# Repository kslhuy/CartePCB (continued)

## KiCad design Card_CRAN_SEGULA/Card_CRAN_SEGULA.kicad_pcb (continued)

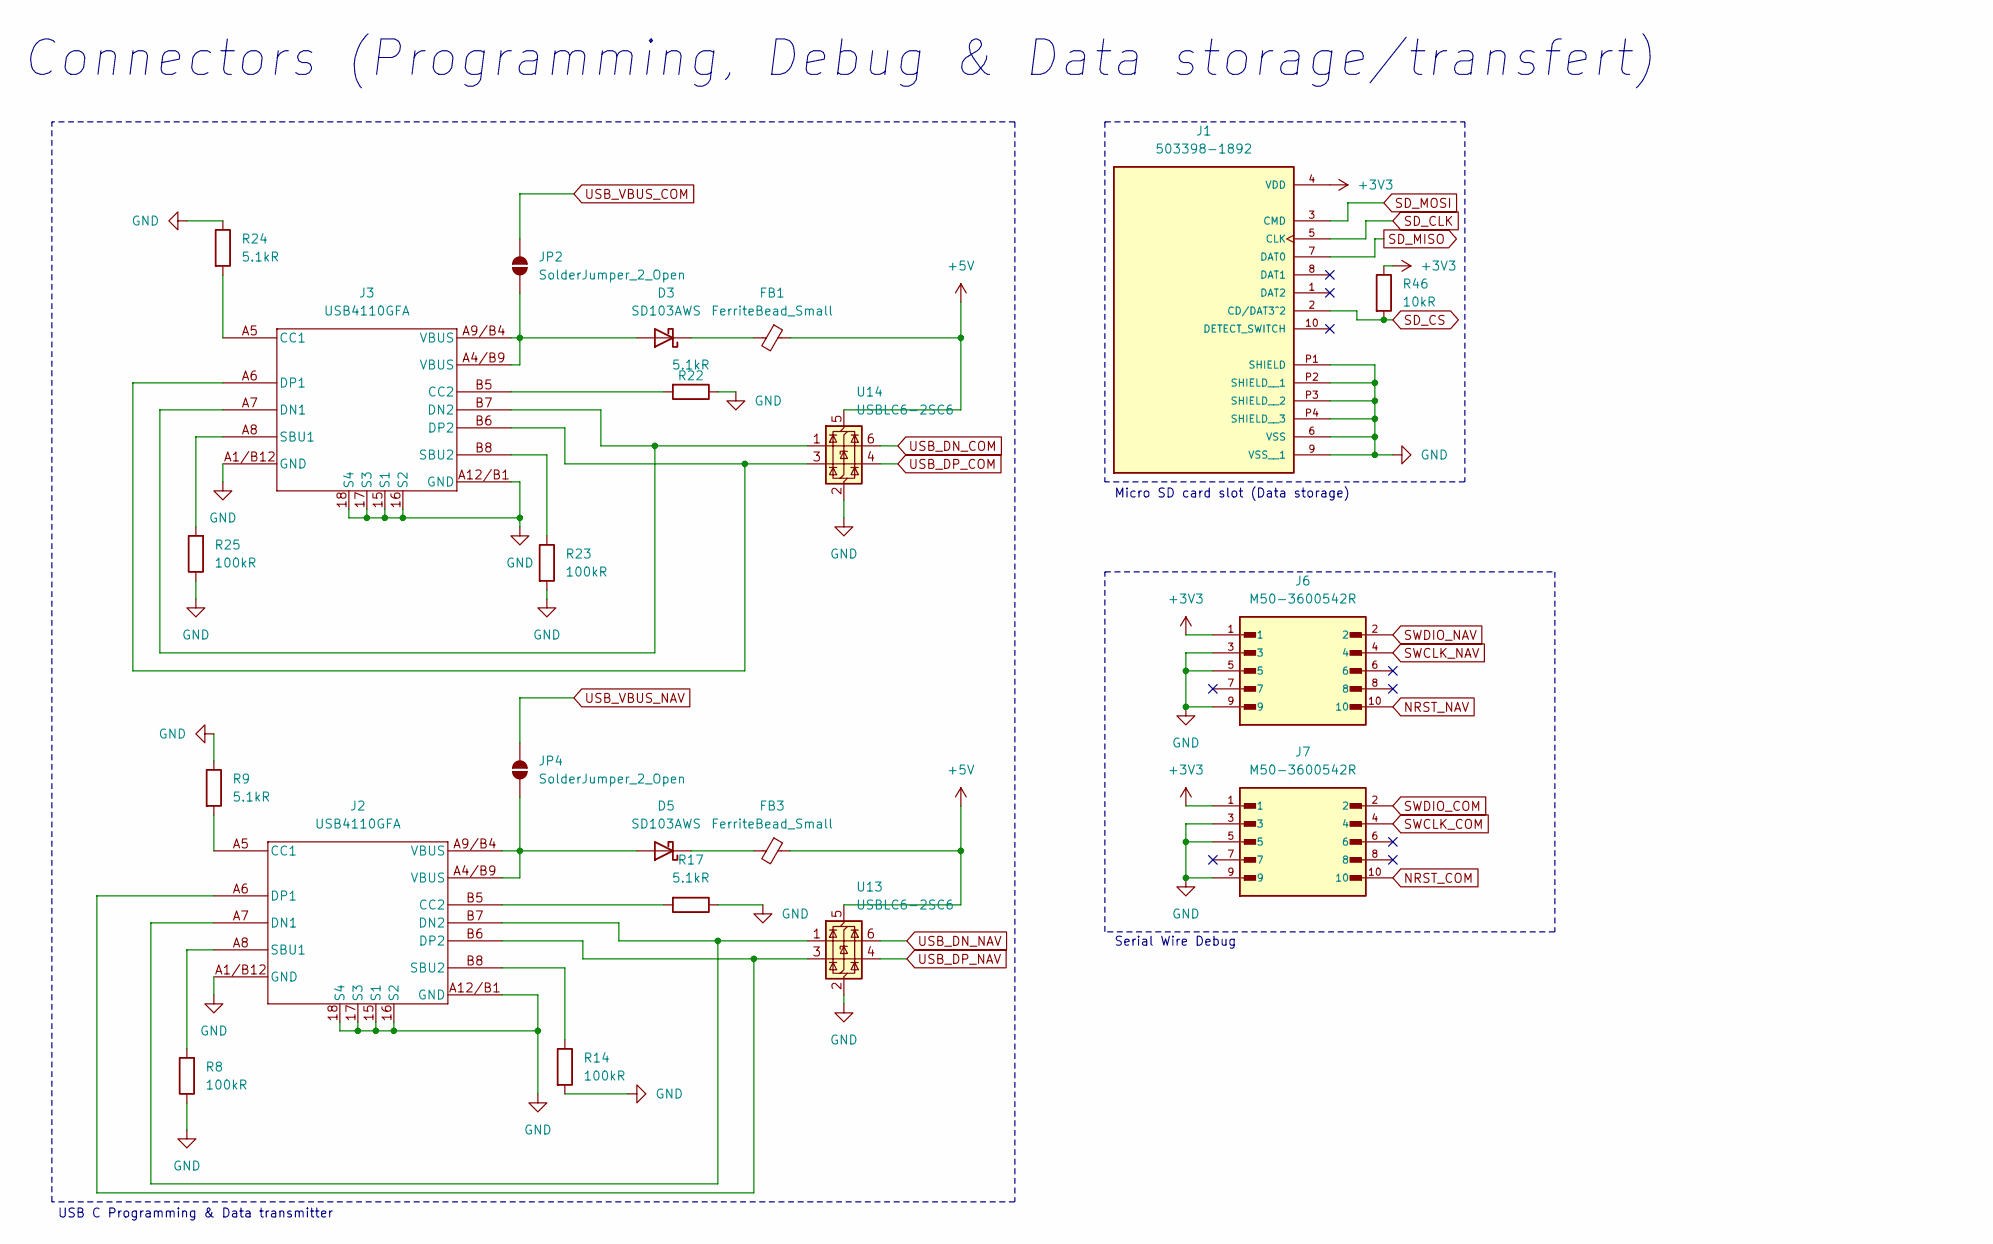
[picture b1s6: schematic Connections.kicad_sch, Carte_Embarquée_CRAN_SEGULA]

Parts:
D3, D5: SD103AWS; D_SOD-323
FB1, FB3: FerriteBead_Small; L_0402_1005Metric
J1: 503398-1892; MOLEX_503398-1892; PARTREV 0
J2, J3: USB4110GFA; USB4110-GF-A_GCT
J6, J7: M50-3600542R; HARWIN_M50-3600542R
JP2, JP4: SolderJumper_2_Open; SolderJumper-2_P1.3mm_Open_RoundedPad1.0x1.5mm
R8, R14, R23, R25: 100kR; RES_ERJ2RKF1003X
R9, R17, R22, R24: 5.1kR; RES_ERJ2RKF5101X
R46: 10kR; RESC1105X40N
U13, U14: USBLC6-2SC6; SOT-23-6

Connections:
+5V: FB1.1, FB3.1, U13.5 (VBUS), U14.5 (VBUS); also elsewhere on the board
GND: J1.6 (VSS), J1.9 (VSS__1), J1.P1 (SHIELD), J1.P2 (SHIELD__1), J1.P3 (SHIELD__2), J1.P4 (SHIELD__3), J2.15 (S1), J2.16 (S2), J2.17 (S3), J2.18 (S4), J2.A1/B12 (GND), J2.A12/B1 (GND), J3.15 (S1), J3.16 (S2), J3.17 (S3), J3.18 (S4), J3.A1/B12 (GND), J3.A12/B1 (GND), J6.3, J6.5, J6.9, J7.3, J7.5, J7.9, R8.1, R9.1, R14.2, R17.1, R22.1, R23.2, R24.1, R25.1, U13.2 (GND), U14.2 (GND); also elsewhere on the board
NRST_COM: J7.10; also elsewhere on the board
NRST_NAV: J6.10; also elsewhere on the board
unnamed: D3.2 (A), J3.A4/B9 (VBUS), J3.A9/B4 (VBUS), JP2.1 (A)
unnamed: D3.1 (K), FB1.2
unnamed: D5.2 (A), J2.A4/B9 (VBUS), J2.A9/B4 (VBUS), JP4.1 (A)
unnamed: D5.1 (K), FB3.2
unnamed: J2.A5 (CC1), R9.2
unnamed: J2.B5 (CC2), R17.2
unnamed: J2.A7 (DN1), J2.B7 (DN2), U13.1 (I/O1)
unnamed: J2.A6 (DP1), J2.B6 (DP2), U13.3 (I/O2)
unnamed: J2.A8 (SBU1), R8.2
unnamed: J2.B8 (SBU2), R14.1
unnamed: J3.A5 (CC1), R24.2
unnamed: J3.B5 (CC2), R22.2
unnamed: J3.A7 (DN1), J3.B7 (DN2), U14.1 (I/O1)
unnamed: J3.A6 (DP1), J3.B6 (DP2), U14.3 (I/O2)
unnamed: J3.A8 (SBU1), R25.2
unnamed: J3.B8 (SBU2), R23.1
SD_CLK: J1.5 (CLK); also elsewhere on the board
SD_CS: J1.2 (CD/DAT3^2), R46.2; also elsewhere on the board
SD_MISO: J1.7 (DAT0); also elsewhere on the board
SD_MOSI: J1.3 (CMD); also elsewhere on the board
SWCLK_COM: J7.4; also elsewhere on the board
SWCLK_NAV: J6.4; also elsewhere on the board
SWDIO_COM: J7.2; also elsewhere on the board
SWDIO_NAV: J6.2; also elsewhere on the board
USB_DN_COM: U14.6 (I/O1); also elsewhere on the board
USB_DN_NAV: U13.6 (I/O1); also elsewhere on the board
USB_DP_COM: U14.4 (I/O2); also elsewhere on the board
USB_DP_NAV: U13.4 (I/O2); also elsewhere on the board
USB_VBUS_COM: JP2.2 (B); also elsewhere on the board
USB_VBUS_NAV: JP4.2 (B); also elsewhere on the board
WIFI_BUCVBATS: J1.4 (VDD), J6.1, J7.1, R46.1; also elsewhere on the board

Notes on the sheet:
Connectors (Programming, Debug & Data storage/transfert)
Micro SD card slot (Data storage)
USB C Programming & Data transmitter
Serial Wire Debug

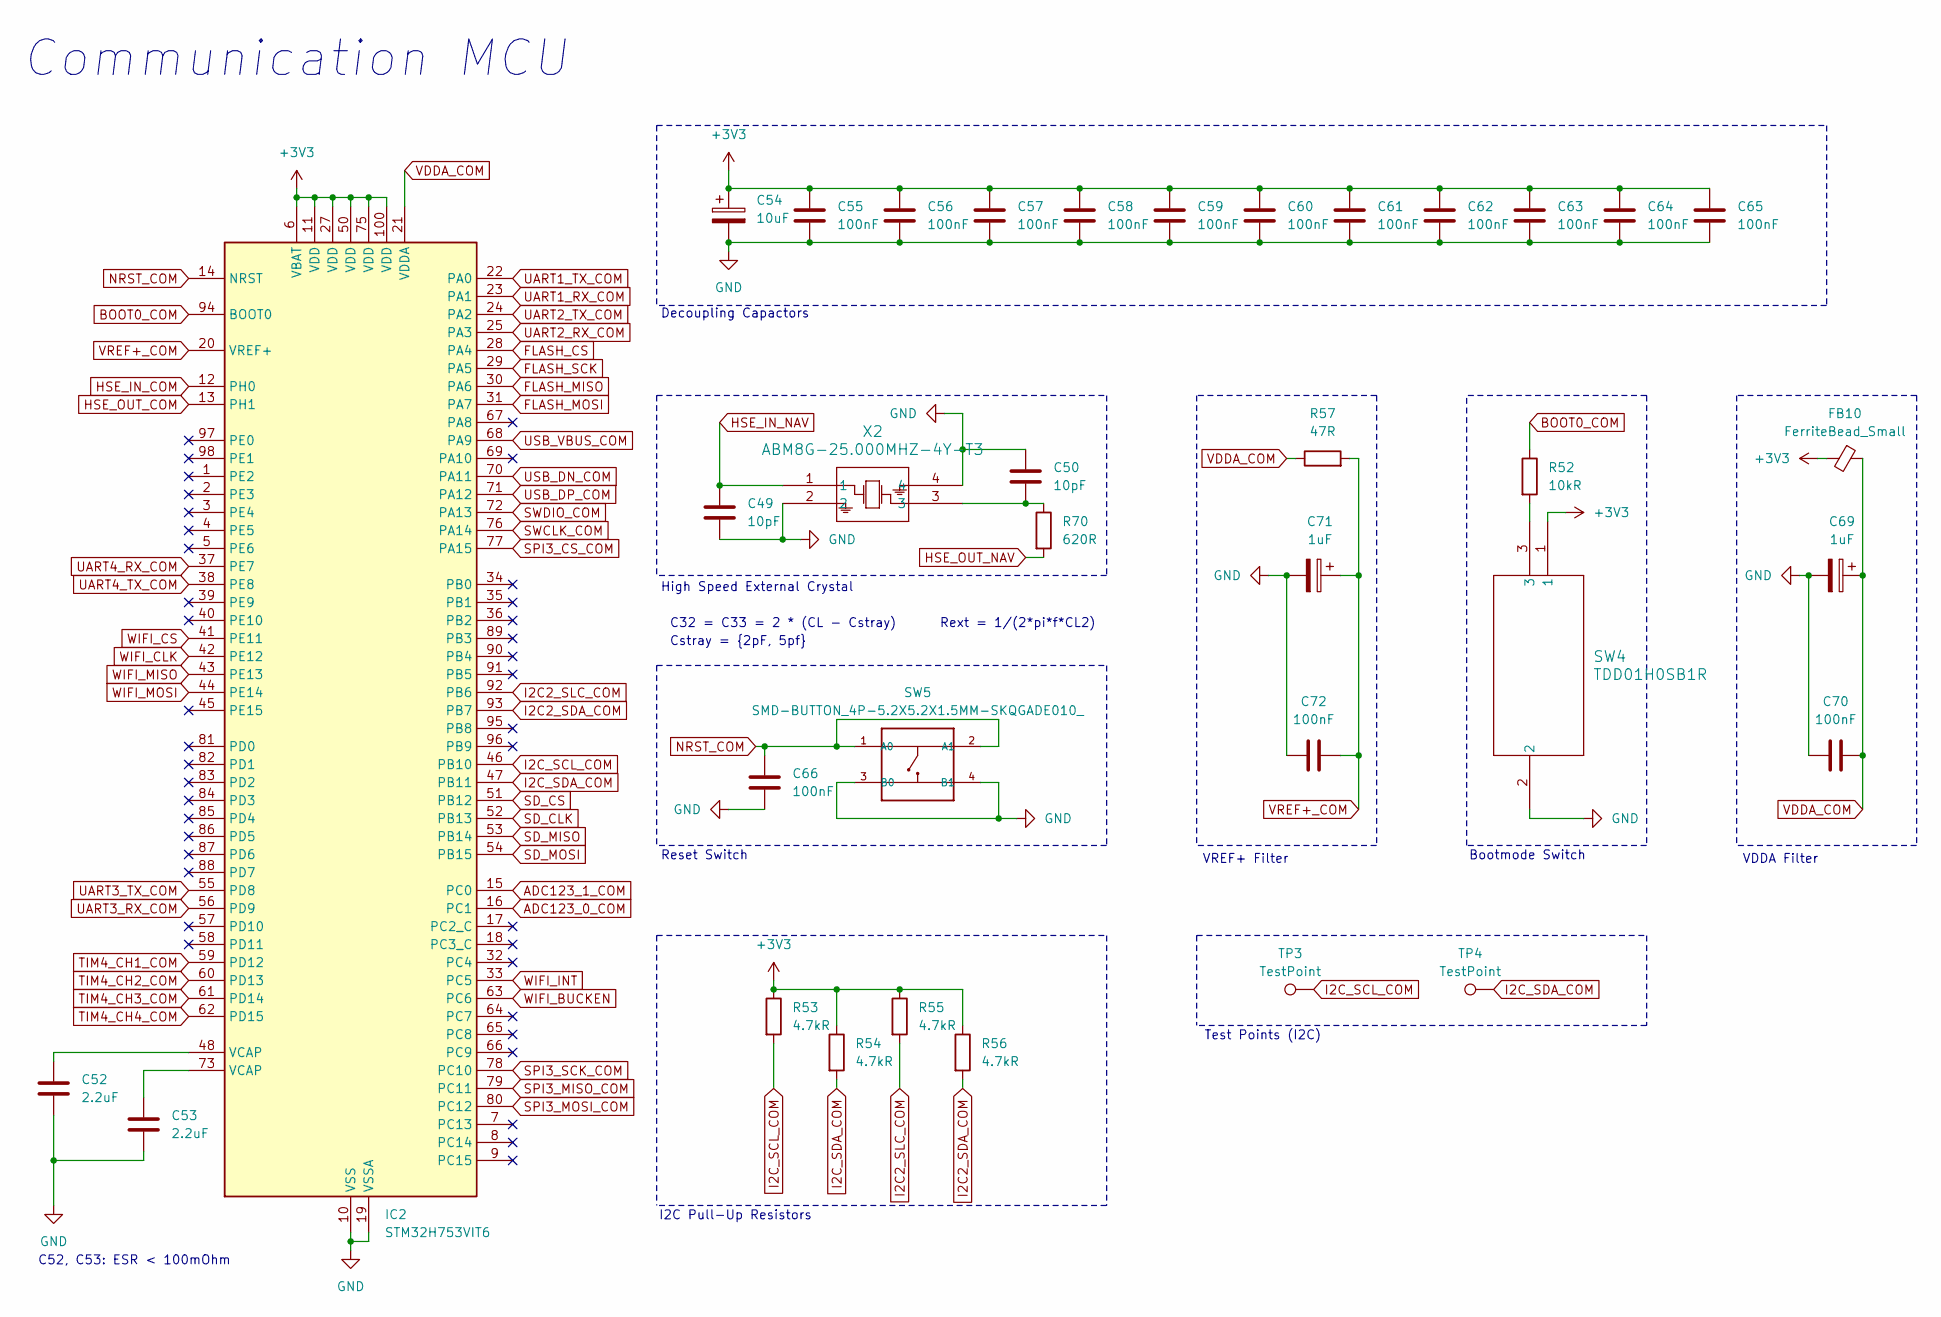
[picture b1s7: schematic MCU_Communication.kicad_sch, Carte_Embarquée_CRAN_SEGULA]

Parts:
C49, C50: 10pF; CAP_0402C_AVX
C52, C53: 2.2uF; CAPC1608X100N
C54: 10uF; CAPMP2.1X1.25_1N_KEM
C55, C56, C57, C58, C59, C60, C61, C62, C63, C64, C65, C66, C70, C72: 100nF; CAPC1005X55N
C69, C71: 1uF; TACL_AVX
FB10: FerriteBead_Small; L_0402_1005Metric
IC2: STM32H753VIT6; LQFP-100_14x14mm_P0.5mm
R52: 10kR; RESC1105X40N
R53, R54, R55, R56: 4.7kR; RESC1005X40N
R57: 47R; RES_ERA2AED470X
R70: 620R; RES_ERJPA3F6200V
SW4: TDD01H0SB1R; SOT_TDDSB1R_CNK
SW5: SMD-BUTTON_4P-5.2X5.2X1.5MM-SKQGADE010_; SW4-SMD-5.2X5.2X1.5MM
TP3, TP4: TestPoint; TestPoint_Pad_D1.5mm
X2: ABM8G-25.000MHZ-4Y-T3; ABM8G_ABR

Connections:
ADC123_0_COM: IC2.16 (PC1); also elsewhere on the board
ADC123_1_COM: IC2.15 (PC0); also elsewhere on the board
BOOT0_COM: IC2.94 (BOOT0), R52.1
FLASH_CS: IC2.28 (PA4); also elsewhere on the board
FLASH_MISO: IC2.30 (PA6); also elsewhere on the board
FLASH_MOSI: IC2.31 (PA7); also elsewhere on the board
FLASH_SCK: IC2.29 (PA5); also elsewhere on the board
GND: C49.2, C50.1, C52.2, C53.2, C54.2, C55.2, C56.2, C57.2, C58.2, C59.2, C60.2, C61.2, C62.2, C63.2, C64.2, C65.2, C66.2, C69.2, C70.1, C71.2, C72.1, IC2.10 (VSS), IC2.19 (VSSA), IC2.26 (VSS), IC2.49 (VSS), IC2.74 (VSS), IC2.99 (VSS), SW4.2, SW5.3 (B0), SW5.4 (B1), X2.2, X2.4; also elsewhere on the board
HSE_IN_COM: IC2.12 (PH0); also elsewhere on the board
HSE_IN_NAV: C49.1, X2.1; also elsewhere on the board
HSE_OUT_COM: IC2.13 (PH1); also elsewhere on the board
HSE_OUT_NAV: R70.2; also elsewhere on the board
I2C2_SDA_COM: IC2.93 (PB7), R56.2; also elsewhere on the board
I2C2_SLC_COM: IC2.92 (PB6), R55.2; also elsewhere on the board
I2C_SCL_COM: IC2.46 (PB10), R53.2, TP3.1; also elsewhere on the board
I2C_SDA_COM: IC2.47 (PB11), R54.2, TP4.1; also elsewhere on the board
NRST_COM: C66.1, IC2.14 (NRST), SW5.1 (A0), SW5.2 (A1); also elsewhere on the board
unnamed: C50.2, R70.1, X2.3
unnamed: C52.1, IC2.48 (VCAP)
unnamed: C53.1, IC2.73 (VCAP)
unnamed: R52.2, SW4.3
SD_CLK: IC2.52 (PB13); also elsewhere on the board
SD_CS: IC2.51 (PB12); also elsewhere on the board
SD_MISO: IC2.53 (PB14); also elsewhere on the board
SD_MOSI: IC2.54 (PB15); also elsewhere on the board
SPI3_CS_COM: IC2.77 (PA15); also elsewhere on the board
SWCLK_COM: IC2.76 (PA14); also elsewhere on the board
SWDIO_COM: IC2.72 (PA13); also elsewhere on the board
TIM4_CH1_COM: IC2.59 (PD12); also elsewhere on the board
TIM4_CH2_COM: IC2.60 (PD13); also elsewhere on the board
TIM4_CH3_COM: IC2.61 (PD14); also elsewhere on the board
TIM4_CH4_COM: IC2.62 (PD15); also elsewhere on the board
UART1_RX_COM: IC2.23 (PA1); also elsewhere on the board
UART1_TX_COM: IC2.22 (PA0); also elsewhere on the board
UART2_RX_COM: IC2.25 (PA3); also elsewhere on the board
UART2_TX_COM: IC2.24 (PA2); also elsewhere on the board
UART3_RX_COM: IC2.56 (PD9); also elsewhere on the board
UART3_TX_COM: IC2.55 (PD8); also elsewhere on the board
UART4_RX_COM: IC2.37 (PE7); also elsewhere on the board
UART4_TX_COM: IC2.38 (PE8); also elsewhere on the board
USB_DN_COM: IC2.70 (PA11); also elsewhere on the board
USB_DP_COM: IC2.71 (PA12); also elsewhere on the board
USB_VBUS_COM: IC2.68 (PA9); also elsewhere on the board
VDDA_COM: C69.1, C70.2, FB10.1, IC2.21 (VDDA), R57.1
VREF+_COM: C71.1, C72.2, IC2.20 (VREF+), R57.2
WIFI_BUCKEN: IC2.63 (PC6); also elsewhere on the board
WIFI_BUCVBATS: C54.1, C55.1, C56.1, C57.1, C58.1, C59.1, C60.1, C61.1, C62.1, C63.1, C64.1, C65.1, FB10.2, IC2.6 (VBAT), IC2.11 (VDD), IC2.27 (VDD), IC2.50 (VDD), IC2.75 (VDD), IC2.100 (VDD), R53.1, R54.1, R55.1, R56.1, SW4.1; also elsewhere on the board
WIFI_CLK: IC2.42 (PE12); also elsewhere on the board
WIFI_CS: IC2.41 (PE11); also elsewhere on the board
WIFI_INT: IC2.33 (PC5); also elsewhere on the board
WIFI_MISO: IC2.43 (PE13); also elsewhere on the board
WIFI_MOSI: IC2.44 (PE14); also elsewhere on the board

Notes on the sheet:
Test Points (I2C)
Decoupling Capactors
C52, C53: ESR < 100mOhm
High Speed External Crystal
Communication MCU
C32 = C33 = 2 * (CL - Cstray)
Rext = 1/(2*pi*f*CL2)
Reset Switch
Cstray = {2pF, 5pf}
Bootmode Switch
VREF+ Filter
I2C Pull-Up Resistors
VDDA Filter

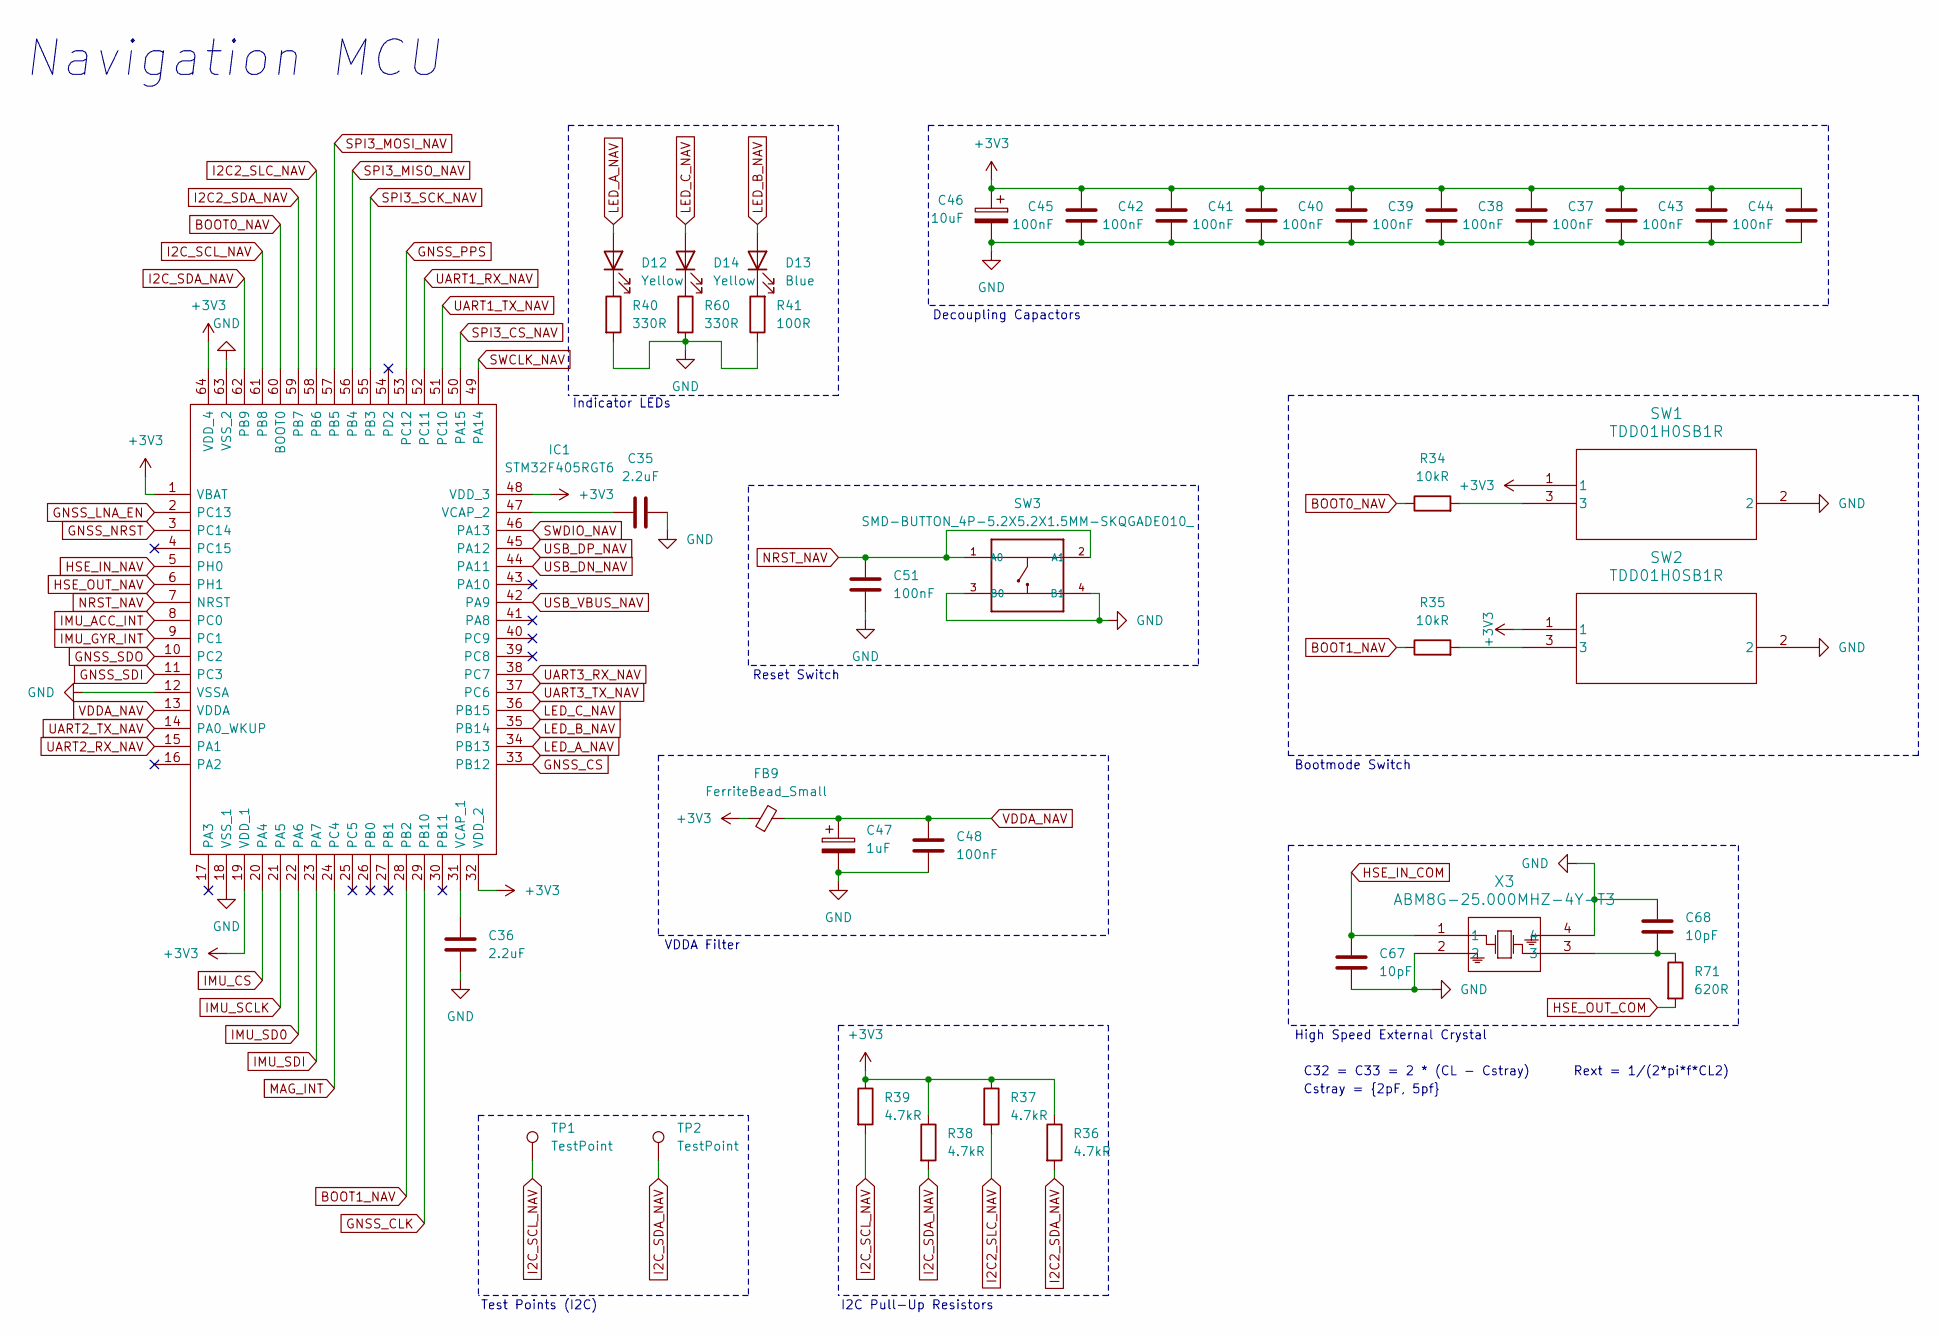
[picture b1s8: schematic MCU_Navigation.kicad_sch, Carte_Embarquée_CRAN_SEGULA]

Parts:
C35, C36: 2.2uF; CAPC1608X100N
C37, C38, C39, C40, C41, C42, C43, C44, C45, C48, C51: 100nF; CAPC1005X55N
C46: 10uF; CAPMP2.1X1.25_1N_KEM
C47: 1uF; TACL_AVX
C67, C68: 10pF; CAP_0402C_AVX
D12, D14: Yellow; 599-0004-007F_DIA
D13: Blue; 599-0091-007F_DIA
FB9: FerriteBead_Small; L_0402_1005Metric
IC1: STM32F405RGT6; QFP50P1200X1200X160-64N; Manufacturer_Part_Number STM32F405RGT6; Mouser Part Number 511-STM32F405RGT6
R34, R35: 10kR; RESC1105X40N
R36, R37, R38, R39: 4.7kR; RESC1005X40N
R40, R60: 330R; RES_ERJPA3D3300V
R41: 100R; RES_ERJPA3D1000V
R71: 620R; RES_ERJPA3F6200V
SW1, SW2: TDD01H0SB1R; SOT_TDDSB1R_CNK
SW3: SMD-BUTTON_4P-5.2X5.2X1.5MM-SKQGADE010_; SW4-SMD-5.2X5.2X1.5MM
TP1, TP2: TestPoint; TestPoint_Pad_D1.5mm
X3: ABM8G-25.000MHZ-4Y-T3; ABM8G_ABR

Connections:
BOOT0_NAV: IC1.60 (BOOT0), R34.1
BOOT1_NAV: IC1.28 (PB2), R35.1
GND: C35.2, C36.2, C37.2, C38.2, C39.2, C40.2, C41.2, C42.2, C43.2, C44.2, C45.2, C46.2, C47.2, C48.2, C51.2, C67.2, C68.1, IC1.12 (VSSA), IC1.18 (VSS_1), IC1.63 (VSS_2), R40.2, R41.1, R60.2, SW1.2, SW2.2, SW3.3 (B0), SW3.4 (B1), X3.2, X3.4; also elsewhere on the board
GNSS_CLK: IC1.29 (PB10); also elsewhere on the board
GNSS_CS: IC1.33 (PB12); also elsewhere on the board
GNSS_LNA_EN: IC1.2 (PC13); also elsewhere on the board
GNSS_NRST: IC1.3 (PC14); also elsewhere on the board
GNSS_PPS: IC1.53 (PC12); also elsewhere on the board
GNSS_SDI: IC1.11 (PC3); also elsewhere on the board
GNSS_SDO: IC1.10 (PC2); also elsewhere on the board
HSE_IN_COM: C67.1, X3.1; also elsewhere on the board
HSE_IN_NAV: IC1.5 (PH0); also elsewhere on the board
HSE_OUT_COM: R71.2; also elsewhere on the board
HSE_OUT_NAV: IC1.6 (PH1); also elsewhere on the board
I2C2_SDA_NAV: IC1.59 (PB7), R36.2; also elsewhere on the board
I2C2_SLC_NAV: IC1.58 (PB6), R37.2; also elsewhere on the board
I2C_SCL_NAV: IC1.61 (PB8), R39.2, TP1.1; also elsewhere on the board
I2C_SDA_NAV: IC1.62 (PB9), R38.2, TP2.1; also elsewhere on the board
IMU_ACC_INT: IC1.8 (PC0); also elsewhere on the board
IMU_CS: IC1.20 (PA4); also elsewhere on the board
IMU_GYR_INT: IC1.9 (PC1); also elsewhere on the board
IMU_SCLK: IC1.21 (PA5); also elsewhere on the board
IMU_SD0: IC1.22 (PA6); also elsewhere on the board
IMU_SDI: IC1.23 (PA7); also elsewhere on the board
LED_A_NAV: D12.2 (A), IC1.34 (PB13)
LED_B_NAV: D13.2 (A), IC1.35 (PB14)
LED_C_NAV: D14.2 (A), IC1.36 (PB15)
MAG_INT: IC1.24 (PC4); also elsewhere on the board
NRST_NAV: C51.1, IC1.7 (NRST), SW3.1 (A0), SW3.2 (A1); also elsewhere on the board
unnamed: C68.2, R71.1, X3.3
unnamed: D12.1 (K), R40.1
unnamed: D13.1 (K), R41.2
unnamed: D14.1 (K), R60.1
unnamed: C36.1, IC1.31 (VCAP_1)
unnamed: C35.1, IC1.47 (VCAP_2)
unnamed: R34.2, SW1.3
unnamed: R35.2, SW2.3
SPI3_CS_COM: IC1.50 (PA15); also elsewhere on the board
SWCLK_NAV: IC1.49 (PA14); also elsewhere on the board
SWDIO_NAV: IC1.46 (PA13); also elsewhere on the board
UART1_RX_NAV: IC1.52 (PC11); also elsewhere on the board
UART1_TX_NAV: IC1.51 (PC10); also elsewhere on the board
UART2_RX_NAV: IC1.15 (PA1); also elsewhere on the board
UART2_TX_NAV: IC1.14 (PA0_WKUP); also elsewhere on the board
UART3_RX_NAV: IC1.38 (PC7); also elsewhere on the board
UART3_TX_NAV: IC1.37 (PC6); also elsewhere on the board
USB_DN_NAV: IC1.44 (PA11); also elsewhere on the board
USB_DP_NAV: IC1.45 (PA12); also elsewhere on the board
USB_VBUS_NAV: IC1.42 (PA9); also elsewhere on the board
VDDA_NAV: C47.1, C48.1, FB9.2, IC1.13 (VDDA)
WIFI_BUCVBATS: C37.1, C38.1, C39.1, C40.1, C41.1, C42.1, C43.1, C44.1, C45.1, C46.1, FB9.1, IC1.1 (VBAT), IC1.19 (VDD_1), IC1.32 (VDD_2), IC1.48 (VDD_3), IC1.64 (VDD_4), R36.1, R37.1, R38.1, R39.1, SW1.1, SW2.1; also elsewhere on the board

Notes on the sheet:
VDDA Filter
Navigation MCU
Bootmode Switch
I2C Pull-Up Resistors
High Speed External Crystal
Cstray = {2pF, 5pf}
Test Points (I2C)
Reset Switch
Rext = 1/(2*pi*f*CL2)
Decoupling Capactors
C32 = C33 = 2 * (CL - Cstray)
Indicator LEDs

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
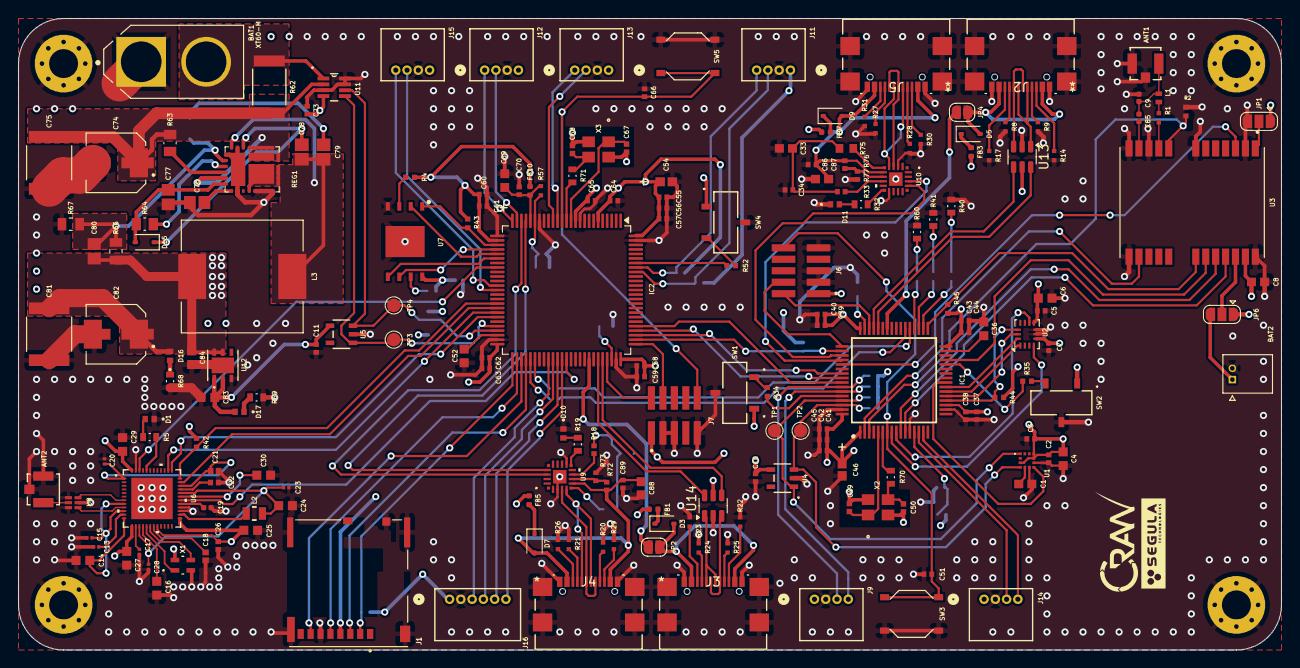
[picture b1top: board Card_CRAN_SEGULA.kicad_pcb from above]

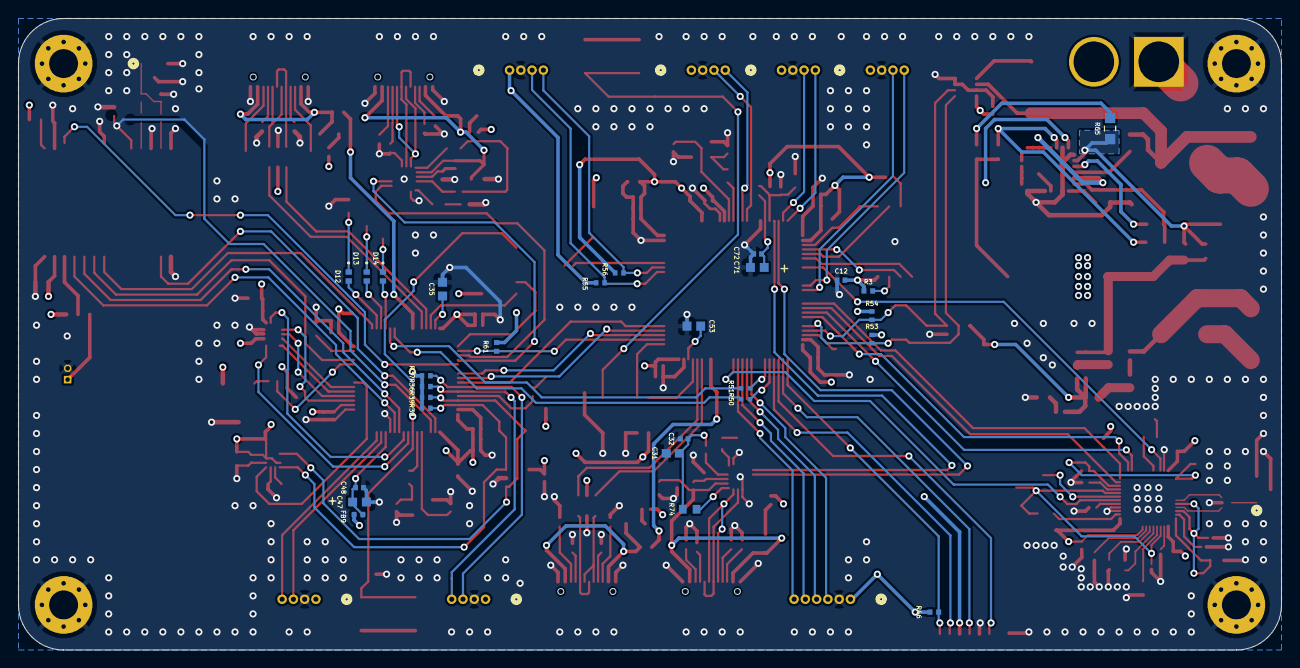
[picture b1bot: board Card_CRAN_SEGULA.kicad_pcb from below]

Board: 4 copper layers, 140.0 x 70.0 mm, 230 parts (28 on the bottom side), 183 nets.

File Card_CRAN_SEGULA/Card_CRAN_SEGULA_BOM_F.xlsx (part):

Reference | Qty | Description | Package | Manufacturer | Reference | Link
ANT1/ANT2 | 2 | U.FL (UMCC)/I-PEX MHFI_Impedance:50Ohm_max_freq:6GHz_see 3D picture for orienta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 | Receptacle, Male Pin | Taoglas Limited | RECE.20279.001E.01 | https://www.digikey.fr/fr/products/detail/taoglas-limited/RE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
BAT1 | 1 | NEGATIVE TERMINAL indicated by DOT on silkscreen | XT60 CONNECTOR | SparkFun Electronics | 10474 | https://www.digikey.fr/en/products/detail/sparkfun-electroni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
BAT2 | 1 | Connector Header Through Hole, Right Angle 2 position | 0.049" (1.25mm) | pin_2x1_0530480210:MOLEX_530480210 Molex | 530480210 | https://www.digikey.fr/en/products/detail/molex/0530480210/2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
C1 | 1 | 220nF_10%_16V_Ceramic_X7R | 0603 (1608 Metric) | KEMET | C0603C224K4RAC7411 | https://www.digikey.fr/en/products/detail/kemet/C0603C224K4R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
C78/C79 | 2 | 100nF_10%_50V_Ceramic_X7R | 0805 (2012 Metric) | KEMET | C0805X104K5RAC3316 | https://www.digikey.fr/en/products/detail/kemet/C0805X104K5R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
C2/C3/C12/C73/C55/C56/C57/C58/C59/C60/C61/C62/C63/C64/C65/C37/C38/C39/C40/C41/C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 | 35 | 100nF_5%_50V_Ceramic_X7S | 0402 (1005 Metric) | Murata Electronics | GRM155C71H104JE19J | https://www.digikey.fr/en/products/detail/murata-electronics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
C15/C20 | 2 | 100nF_10%_16V_Ceramic_X7S | 0201 (0603 Metric) | Murata Electronics | GRM033C71C104KE14D | https://www.digikey.fr/en/products/detail/murata-electronics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
C46/C54 | 2 | 10uF_Molded Tantalum Polymer_10 V_ 200mOhm @ 100kHz (or 300mOhm)_1000 Hrs @ 105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 | 0805 (2012 Metric) | KEMET | T529P106M010AAE200 | https://www.digikey.fr/en/products/detail/kemet/T529P106M010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
C4/C83/C84 | 2 | 10uF_10%_25V_Ceramic_X5R | 0603 (1608 Metric) | Murata Electronics | GRM188R61E106KA73J | https://www.digikey.fr/en/products/detail/murata-electronics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
C5 | 1 | 0.1uF_5%_50V Ceramic_X7S | 0402 (1005 Metric) | Murata Electronics | GRM155C71H104JE19D | https://www.digikey.fr/en/products/detail/murata-electronics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
C35/C36/C52/C53 | 4 | 2.2uF_10%_50V_Ceramic_X5R | 0603 (1608 Metric) | Murata Electronics | GRM188R61H225KE11D | https://www.digikey.fr/en/products/detail/murata-electronics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
C6 | 1 | 2.2uF_10%_50V_Ceramic_X5R | 0603 (1608 Metric) | Murata Electronics | GRM188R61H225KE11D | https://www.digikey.fr/en/products/detail/murata-electronics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
C76/C77 | 2 | 2.2 µF_10%_16V_Ceramic_X7R | 0805 (2012 Metric) | KEMET | C0805C225K4REC7210 | https://www.digikey.fr/en/products/detail/kemet/C0805C225K4R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
C16 | 1 | 2.2uF_10%_16V_Ceramic_X7S | 0603 (1608 Metric) | Murata Electronics | GRM188C71C225KE11J | https://www.digikey.fr/en/products/detail/murata-electronics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
C21 | 1 | 2.2uF_Ceramic_25V_X5R_10% | 0402 (1005 Metric) | Murata Electronics | GRM155R61E225KE11D | https://www.digikey.fr/en/products/detail/murata-electronics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
C29/C30 | 2 | 2.2uF_10%_16V_Ceramic_X7S | 0603 (1608 Metric) | Murata Electronics | GRM188C71C225KE11J | https://www.digikey.fr/en/products/detail/murata-electronics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
C7/C9/C19 | 3 | 10nF_Ceramic_25V_X7R_5% | 0402 (1005 Metric) | KEMET | C0402C103J3RACAUTO | https://www.digikey.fr/en/products/detail/kemet/C0402C103J3R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
C31/C33/C87/C88 | 4 | 1uF_10%_25V_Ceramic_X5R | 0603 (1608 Metric) | TDK Corporation | C1608X5R1E105K080AC | https://www.digikey.fr/en/products/detail/tdk-corporation/C1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
C47/C69/C71 | 3 | 1uF_Molded_Tantalum_10 V_7.5Ohm_Polarity indicated by + on silkscreen" | 0603 (1608 Metric) | KYOCERA AVX | TACL105K010XTA | https://www.digikey.fr/en/products/detail/kyocera-avx/TACL10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
C8 | 1 | 1uF_-20%_+80%_25V_Ceramic_Y5V (F) | 0603 (1608 Metric) | KEMET | C0603C105Z3VACTU | https://www.digikey.fr/en/products/detail/kemet/C0603C105Z3V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
C22 | 1 | 1uF_10%_16V_Ceramic_X6S | 0402 (1005 Metric) | Murata Electronics | GRM155C81C105KE15D | https://www.digikey.fr/en/products/detail/murata-electronics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
C26 | 1 | 1uF_Ceramic_35V_X5R_10% | 0402 (1005 Metric) | Murata Electronics | GRM155R6YA105KE11D | https://www.digikey.fr/en/products/detail/murata-electronics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
C18 | 1 | 1uF_Ceramic_10V_X7S_10% | 0402 (1005 Metric) | Murata Electronics | GCM155C71A105KE38D | https://www.digikey.fr/en/products/detail/murata-electronics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
C13/C23 | 2 | 0.47uF_Ceramic_6.3V_X5R_10% | 0201 (0603 Metric) | Murata Electronics | GRM033R60J474KE90J | https://www.digikey.fr/en/products/detail/murata-electronics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
C14/C24/C25/C27 | 4 | 4.7uF_Ceramic_25V_X6S_10% | 0603 (1608 Metric) | Murata Electronics | GRM188C81E475KE11D | https://www.digikey.fr/en/products/detail/murata-electronics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
C17 | 1 | 22nF_10%_10V_Ceramic_X5R | 0201 (0603 Metric) | Murata Electronics | GRM033R61A223KE84D | https://www.digikey.fr/en/products/detail/murata-electronics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
C28 | 1 | 0.22uF_Ceramic_10V_X5R_10% | 0201 (0603 Metric) | Murata Electronics | GRM033R61A224KE90D | https://www.digikey.fr/en/products/detail/murata-electronics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
C49/C50/C67/C68 | 4 | 10pF_5%_50V_Ceramic_C0G_NP0 | 0402 (1005 Metric) | KYOCERA AVX | KGM05ACG1H100JH | https://www.digikey.fr/en/products/detail/kyocera-avx/KGM05A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
C74/C82 | 2 | 100 µF_35V_Aluminum Electrolytic_160mOhm @ 100kHz_2000 Hrs @ 105°C_Low ESR_High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 | Radial, Can - SMD | Panasonic Electronic Components | EEE-FPV101XAV | https://www.digikey.fr/en/products/detail/panasonic-electron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
C75/C81 | 2 | 47uF_20% 35V Ceramic Capacitor X7R_Low ESL | 2220 (5750 Metric) | TDK Corporation | C5750X7R1V476M230KC | https://www.digikey.fr/en/products/detail/tdk-corporation/C5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
C80 | 1 | 4.7nF_5%_25V_Ceramic_C0G_NP0 | 0805 (2012 Metric) | KEMET | C0805C472J3GEC7210 | https://www.mouser.fr/ProductDetail/KEMET/C0805C472J3GEC7210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
C85 | 1 | 22pF_5%_10V_Ceramic_C0G_NP0 | 0402 (1005 Metric) | KEMET | C0402C220J8GACTU | https://www.digikey.fr/en/products/detail/kemet/C0402C220J8G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
D1/D13 | 2 | Blue 470nm LED Indication - Discrete 3.2V | 0603 (1608 Metric) | Dialight | 5990091007F | https://www.digikey.fr/en/products/detail/dialight/599009100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
D3/D5/D7/D9/D15 | 5 | DIODE SCHOTTKY 40V 350MA_Surface Mount | SOD-323 | Diodes Incorporated | SD103AWS-7-F | https://www.digikey.fr/en/products/detail/diodes-incorporate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
D10/D11 | 2 | Red 633nm LED Indication - Discrete 2.1V | 0603 (1608 Metric) | Dialight | 5990010007F | https://www.digikey.fr/en/products/detail/dialight/599001000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
D12/D14 | 2 | Yellow 590nm LED Indication - Discrete 2.1V | 0603 (1608 Metric) | Dialight | 5990040007F | https://www.digikey.fr/en/products/detail/dialight/599004000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
D16/D17 | 2 | Green 525nm LED Indication - Discrete 3.1V | 0603 (1608 Metric) | Dialight | 5990081007F | https://www.digikey.fr/en/products/detail/dialight/599008100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
FB1/FB3/FB5/FB7/FB9/FB10 | 6 | 120 Ohms @ 100 MHz 1 Power Line Ferrite Bead_2A 55mOhm | 0402 (1005 Metric) | TDK Corporation | MPZ1005S121HT000 | https://www.digikey.fr/en/products/detail/tdk-corporation/MP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
IC1 | 1 | ARM® Cortex®-M4 STM32F4 Microcontroller IC 32-Bit Single-Core 168MHz 1MB (1M x 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 | 64-LQFP (10x10) | STMicroelectronics | STM32F405RGT6 | https://www.digikey.fr/en/products/detail/stmicroelectronics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
IC2 | 1 | ARM® Cortex®-M7 STM32H7 Microcontroller IC 32-Bit Single-Core 480MHz 2MB (2M x 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 | 100-LQFP (14x14) | STMicroelectronics | STM32H753VIT6 | https://www.digikey.fr/en/products/detail/stmicroelectronics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
J1 | 1 | 9 (8 + 1) Position Card Connector and Ejector Secure Digital - microSD™ Surface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 |  | Molex | 5033981892 | https://www.digikey.fr/en/products/detail/molex/5033981892/4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
J2/J3/J4/J5 | 4 | USB 2.0 Receptacle Connector 24 (16+8 Dummy) Position Surface Mount_Right Angle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 | USB-C (USB TYPE-C) | GCT | USB4110-GF-A | https://www.digikey.fr/en/products/detail/gct/USB4110-GF-A/1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
J6/J7 | 2 | Connector Header Surface Mount 10 position | 0.050" (1.27mm) | Harwin Inc. | M50-3600542R | https://www.digikey.fr/en/products/detail/harwin-inc/M50-360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
J9/J11/J12/J13/J14/J15 | 6 | Connector Header Through Hole, Right Angle 4 position | 0.049" (1.25mm) | Molex | 530480410 | https://www.digikey.fr/en/products/detail/molex/0530480410/2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
J16 | 1 | Connector Header Through Hole, Right Angle 6 position | 0.049" (1.25mm) | Molex | 530480610 | https://www.digikey.fr/en/products/detail/molex/0530480610/2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

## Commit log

2026-03-03 init
2026-03-04 connect SPI UART ok IMU
2026-06-05 GPS work
